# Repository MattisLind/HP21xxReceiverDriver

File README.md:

### HP 21xx IO bus driver and receiver

This project aims to create replacement for the 75121 driver since they are quite expensive nowadays. In addition to that there is a design for a receiver that is CMOS 3V compatible.

The driver and receiver has been tested on a bread board using through hole mounted components and this is a layout using surface mount parts where six receivers or drivers have been combined into one DIP 24 compatible space.

I recognised that  the pullups on the driver inputs where pulling to 5V through a 2k resistor. To be fully 3.3V compliant this should of course be 3.3V. Since there are no 3.3V regulator on the driver I added a 3.3V output on the receiver which can be connected to the driver input.

The new schematic, layout and production files has been updated and seems to look right. They have not been tested though.

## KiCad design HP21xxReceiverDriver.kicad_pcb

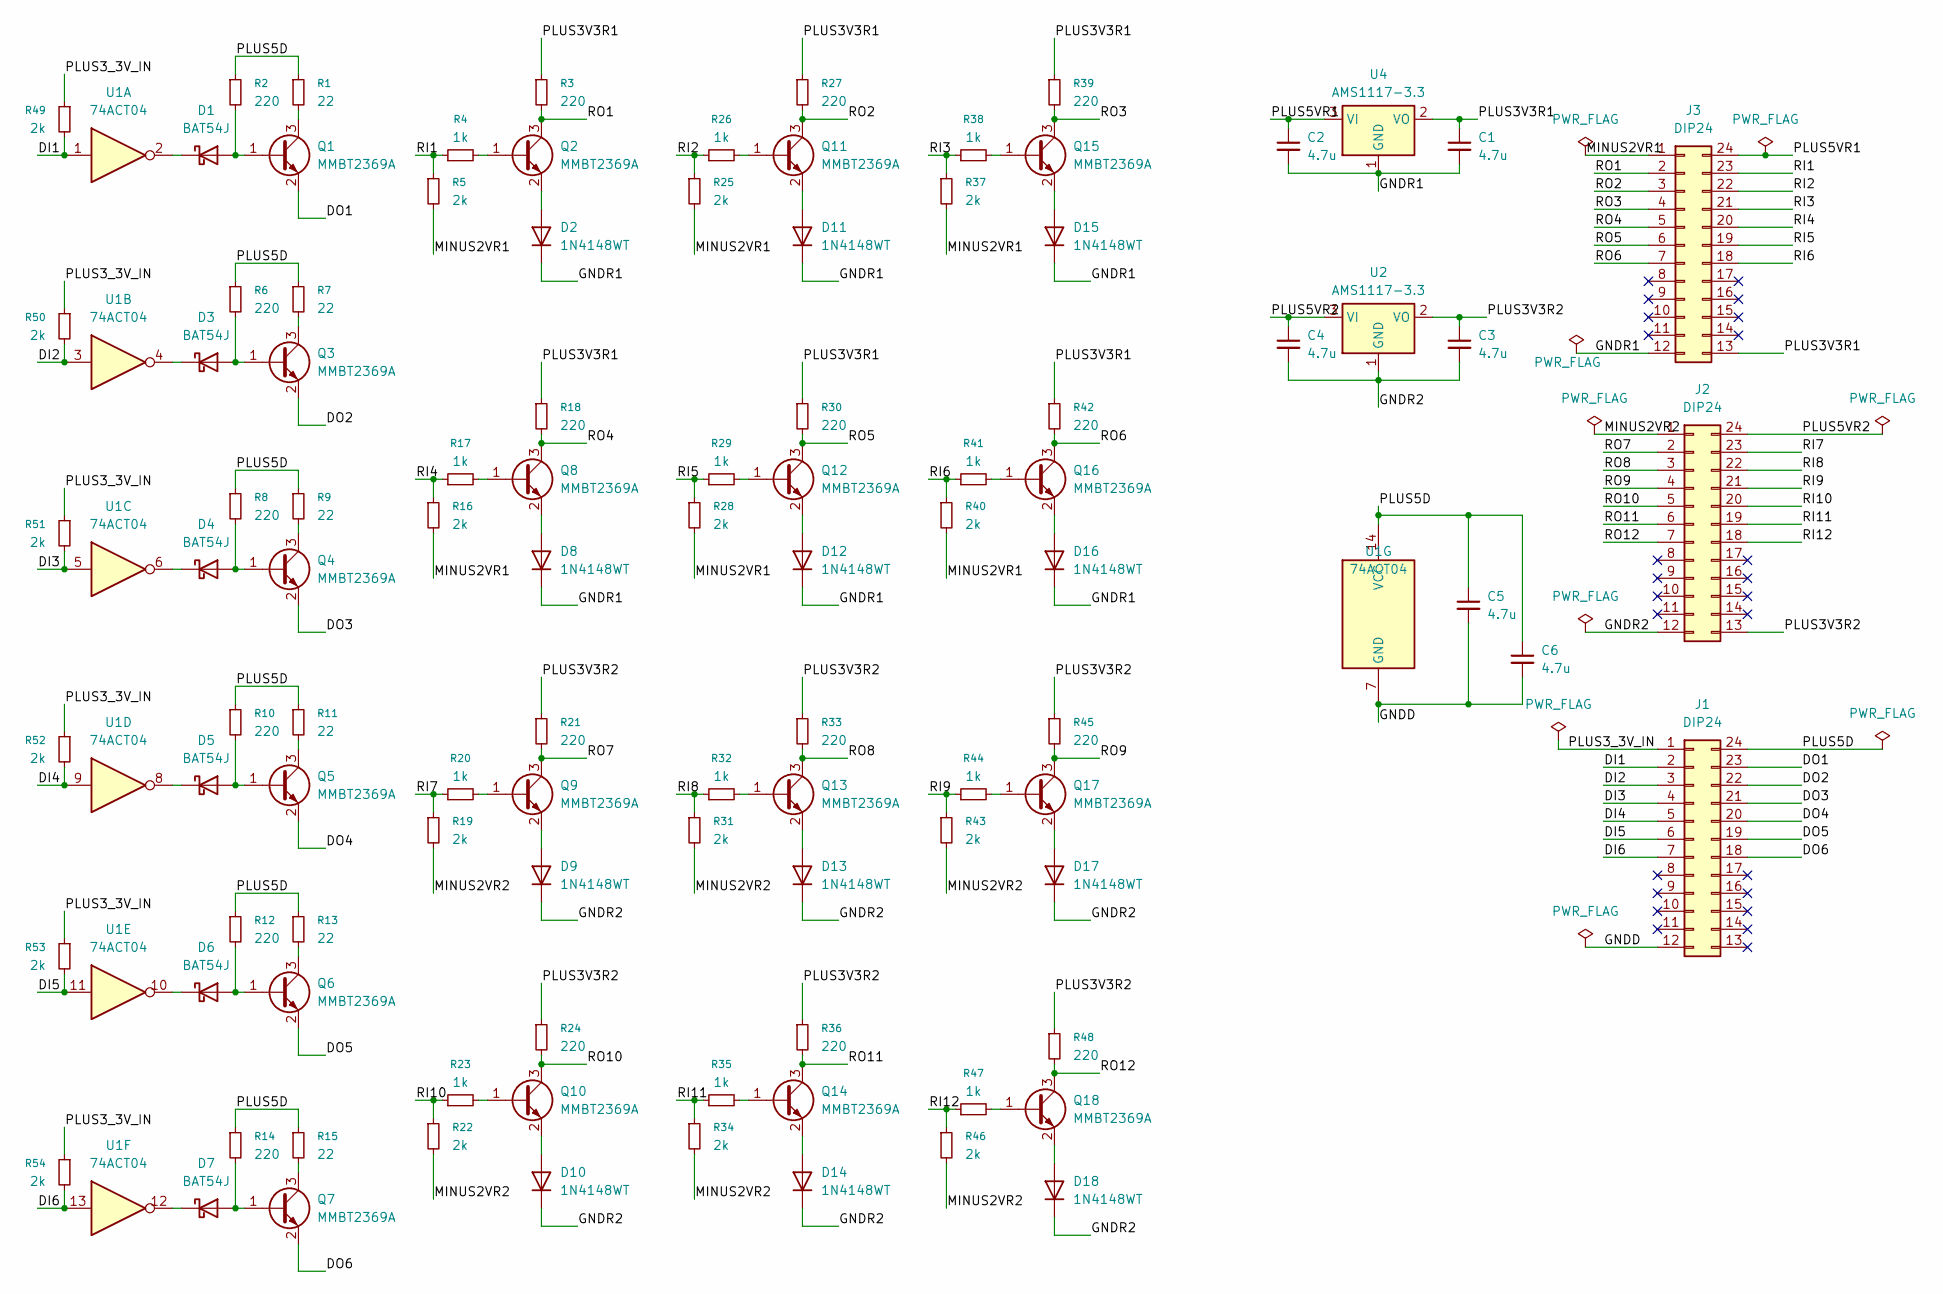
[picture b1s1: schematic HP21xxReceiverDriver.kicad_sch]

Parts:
C1, C2, C3, C4, C5, C6: 4.7u; C_0402_1005Metric; LCSC C23733
D1, D3, D4, D5, D6, D7: BAT54J; D_SOD-523; LCSC C51315114
D2, D8, D9, D10, D11, D12, D13, D14, D15, D16, D17, D18: 1N4148WT; D_SOD-523; LCSC C727112
J1, J2, J3: DIP24; DIP-24_18.0mmx34.29mm_W15.24mm
Q1, Q2, Q3, Q4, Q5, Q6, Q7, Q8, Q9, Q10, Q11, Q12, Q13, Q14, Q15, Q16, Q17, Q18: MMBT2369A; SOT-23; LCSC C94404
R1, R7, R9, R11, R13, R15: 22; R_0805_2012Metric; LCSC C17561
R2, R3, R6, R8, R10, R12, R14, R18, R21, R24, R27, R30, R33, R36, R39, R42, R45, R48: 220; R_0402_1005Metric; LCSC C25091
R4, R17, R20, R23, R26, R29, R32, R35, R38, R41, R44, R47: 1k; R_0402_1005Metric; LCSC C11702
R5, R16, R19, R22, R25, R28, R31, R34, R37, R40, R43, R46, R49, R50, R51, R52, R53, R54: 2k; R_0402_1005Metric; LCSC C4109
U1: 74ACT04; SOIC-14_3.9x8.7mm_P1.27mm; LCSC C5490
U2, U4: AMS1117-3.3; SOT-223-3_TabPin2; LCSC C18164485

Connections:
/DI1: J1.2, R49.2, U1.1
/DI2: J1.3, R50.2, U1.3
/DI3: J1.4, R51.2, U1.5
/DI4: J1.5, R52.2, U1.9
/DI5: J1.6, R53.2, U1.11
/DI6: J1.7, R54.2, U1.13
/DO1: J1.23, Q1.2 (E)
/DO2: J1.22, Q3.2 (E)
/DO3: J1.21, Q4.2 (E)
/DO4: J1.20, Q5.2 (E)
/DO5: J1.19, Q6.2 (E)
/DO6: J1.18, Q7.2 (E)
/GNDD: C5.2, C6.2, J1.12, U1.7 (GND)
/GNDR1: C1.2, C2.2, D2.1 (K), D8.1 (K), D11.1 (K), D12.1 (K), D15.1 (K), D16.1 (K), J3.12, U4.1 (GND)
/GNDR2: C3.2, C4.2, D9.1 (K), D10.1 (K), D13.1 (K), D14.1 (K), D17.1 (K), D18.1 (K), J2.12, U2.1 (GND)
/MINUS2VR1: J3.1, R5.2, R16.2, R25.2, R28.2, R37.2, R40.2
/MINUS2VR2: J2.1, R19.2, R22.2, R31.2, R34.2, R43.2, R46.2
/PLUS3V3R1: C1.1, J3.13, R3.1, R18.1, R27.1, R30.1, R39.1, R42.1, U4.2 (VO)
/PLUS3V3R2: C3.1, J2.13, R21.1, R24.1, R33.1, R36.1, R45.1, R48.1, U2.2 (VO)
/PLUS3_3V_IN: J1.1, R49.1, R50.1, R51.1, R52.1, R53.1, R54.1
/PLUS5D: C5.1, C6.1, J1.24, R1.1, R2.1, R6.1, R7.1, R8.1, R9.1, R10.1, R11.1, R12.1, R13.1, R14.1, R15.1, U1.14 (VCC)
/PLUS5VR1: C2.1, J3.24, U4.3 (VI)
/PLUS5VR2: C4.1, J2.24, U2.3 (VI)
/RI1: J3.23, R4.1, R5.1
/RI2: J3.22, R25.1, R26.1
/RI3: J3.21, R37.1, R38.1
/RI4: J3.20, R16.1, R17.1
/RI5: J3.19, R28.1, R29.1
/RI6: J3.18, R40.1, R41.1
/RI7: J2.23, R19.1, R20.1
/RI8: J2.22, R31.1, R32.1
/RI9: J2.21, R43.1, R44.1
/RI10: J2.20, R22.1, R23.1
/RI11: J2.19, R34.1, R35.1
/RI12: J2.18, R46.1, R47.1
/RO1: J3.2, Q2.3 (C), R3.2
/RO2: J3.3, Q11.3 (C), R27.2
/RO3: J3.4, Q15.3 (C), R39.2
/RO4: J3.5, Q8.3 (C), R18.2
/RO5: J3.6, Q12.3 (C), R30.2
/RO6: J3.7, Q16.3 (C), R42.2
/RO7: J2.2, Q9.3 (C), R21.2
/RO8: J2.3, Q13.3 (C), R33.2
/RO9: J2.4, Q17.3 (C), R45.2
/RO10: J2.5, Q10.3 (C), R24.2
/RO11: J2.6, Q14.3 (C), R36.2
/RO12: J2.7, Q18.3 (C), R48.2
unnamed: D1.2 (A), Q1.1 (B), R2.2
unnamed: D1.1 (K), U1.2
unnamed: D2.2 (A), Q2.2 (E)
unnamed: D3.2 (A), Q3.1 (B), R6.2
unnamed: D3.1 (K), U1.4
unnamed: D4.2 (A), Q4.1 (B), R8.2
unnamed: D4.1 (K), U1.6
unnamed: D5.2 (A), Q5.1 (B), R10.2
unnamed: D5.1 (K), U1.8
unnamed: D6.2 (A), Q6.1 (B), R12.2
unnamed: D6.1 (K), U1.10
unnamed: D7.2 (A), Q7.1 (B), R14.2
unnamed: D7.1 (K), U1.12
unnamed: D8.2 (A), Q8.2 (E)
unnamed: D9.2 (A), Q9.2 (E)
unnamed: D10.2 (A), Q10.2 (E)
unnamed: D11.2 (A), Q11.2 (E)
unnamed: D12.2 (A), Q12.2 (E)
unnamed: D13.2 (A), Q13.2 (E)
unnamed: D14.2 (A), Q14.2 (E)
unnamed: D15.2 (A), Q15.2 (E)
unnamed: D16.2 (A), Q16.2 (E)
unnamed: D17.2 (A), Q17.2 (E)
unnamed: D18.2 (A), Q18.2 (E)
unnamed: Q1.3 (C), R1.2
unnamed: Q2.1 (B), R4.2
unnamed: Q3.3 (C), R7.2
unnamed: Q4.3 (C), R9.2
unnamed: Q5.3 (C), R11.2
unnamed: Q6.3 (C), R13.2
unnamed: Q7.3 (C), R15.2
unnamed: Q8.1 (B), R17.2
unnamed: Q9.1 (B), R20.2
unnamed: Q10.1 (B), R23.2
unnamed: Q11.1 (B), R26.2
unnamed: Q12.1 (B), R29.2
unnamed: Q13.1 (B), R32.2
unnamed: Q14.1 (B), R35.2
unnamed: Q15.1 (B), R38.2
unnamed: Q16.1 (B), R41.2
unnamed: Q17.1 (B), R44.2
unnamed: Q18.1 (B), R47.2

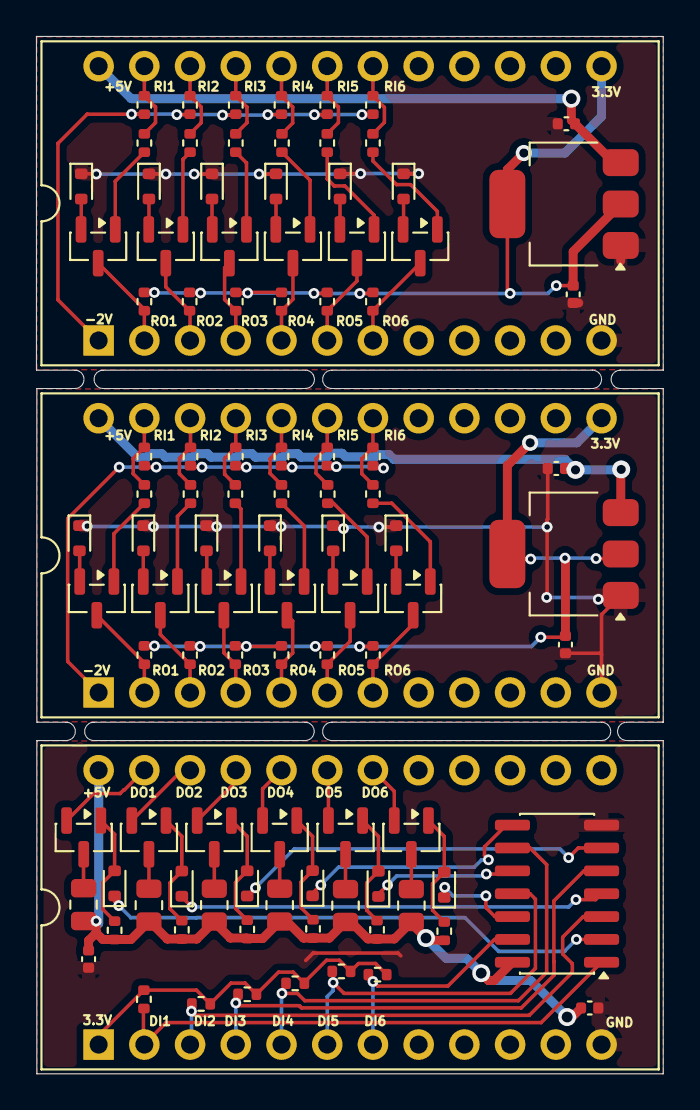
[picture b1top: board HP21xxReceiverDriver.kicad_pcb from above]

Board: 2 copper layers, 34.8 x 57.6 mm, 102 parts (0 on the bottom side), 89 nets.

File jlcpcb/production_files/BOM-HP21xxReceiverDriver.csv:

Comment,Designator,Footprint,LCSC,Quantity
1N4148WT,"D10,D11,D12,D13,D14,D15,D16,D17,D18,D2,D8,D9",D_SOD-523,C727112,12
1k,"R17,R20,R23,R26,R29,R32,R35,R38,R4,R41,R44,R47",R_0402_1005Metric,C11702,12
22,"R1,R11,R13,R15,R7,R9",R_0805_2012Metric,C17561,6
220,"R10,R12,R14,R18,R2,R21,R24,R27,R3,R30,R33,R36,R39,R42,R45,R48,R6,R8",R_0402_1005Metric,C25091,18
2k,"R16,R19,R22,R25,R28,R31,R34,R37,R40,R43,R46,R49,R5,R50,R51,R52,R53,R54",R_0402_1005Metric,C4109,18
4.7u,"C1,C2,C3,C4,C5,C6",C_0402_1005Metric,C23733,6
74ACT04,U1,SOIC-14_3.9x8.7mm_P1.27mm,C5490,1
AMS1117-3.3,"U2,U4",SOT-223-3_TabPin2,C18164485,2
BAT54J,"D1,D3,D4,D5,D6,D7",D_SOD-523,C51315114,6
MMBT2369A,"Q1,Q10,Q11,Q12,Q13,Q14,Q15,Q16,Q17,Q18,Q2,Q3,Q4,Q5,Q6,Q7,Q8,Q9",SOT-23,C94404,18
DIP24,J2,DIP-24_18.0mmx34.29mm_W15.24mm,,1
DIP24,J1,DIP-24_18.0mmx34.29mm_W15.24mm,,1
DIP24,J3,DIP-24_18.0mmx34.29mm_W15.24mm,,1

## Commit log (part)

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2026-03-18 Added a PDF for the schematic.
2026-03-18 Add README content for HP 21xx IO bus project
    Added project description for HP 21xx IO bus driver and receiver.
2026-03-21 Changed to 2k terminating resistors.
